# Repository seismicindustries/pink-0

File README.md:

<!--- View this project on [CADLAB.io](https://cadlab.io/project/1079). -->

# (s)pink-0

This repository contains the source code and the schematics for an Ableton Link to clock/reset converter.

And the necessary changes & hardware files for the spink-0 adaption

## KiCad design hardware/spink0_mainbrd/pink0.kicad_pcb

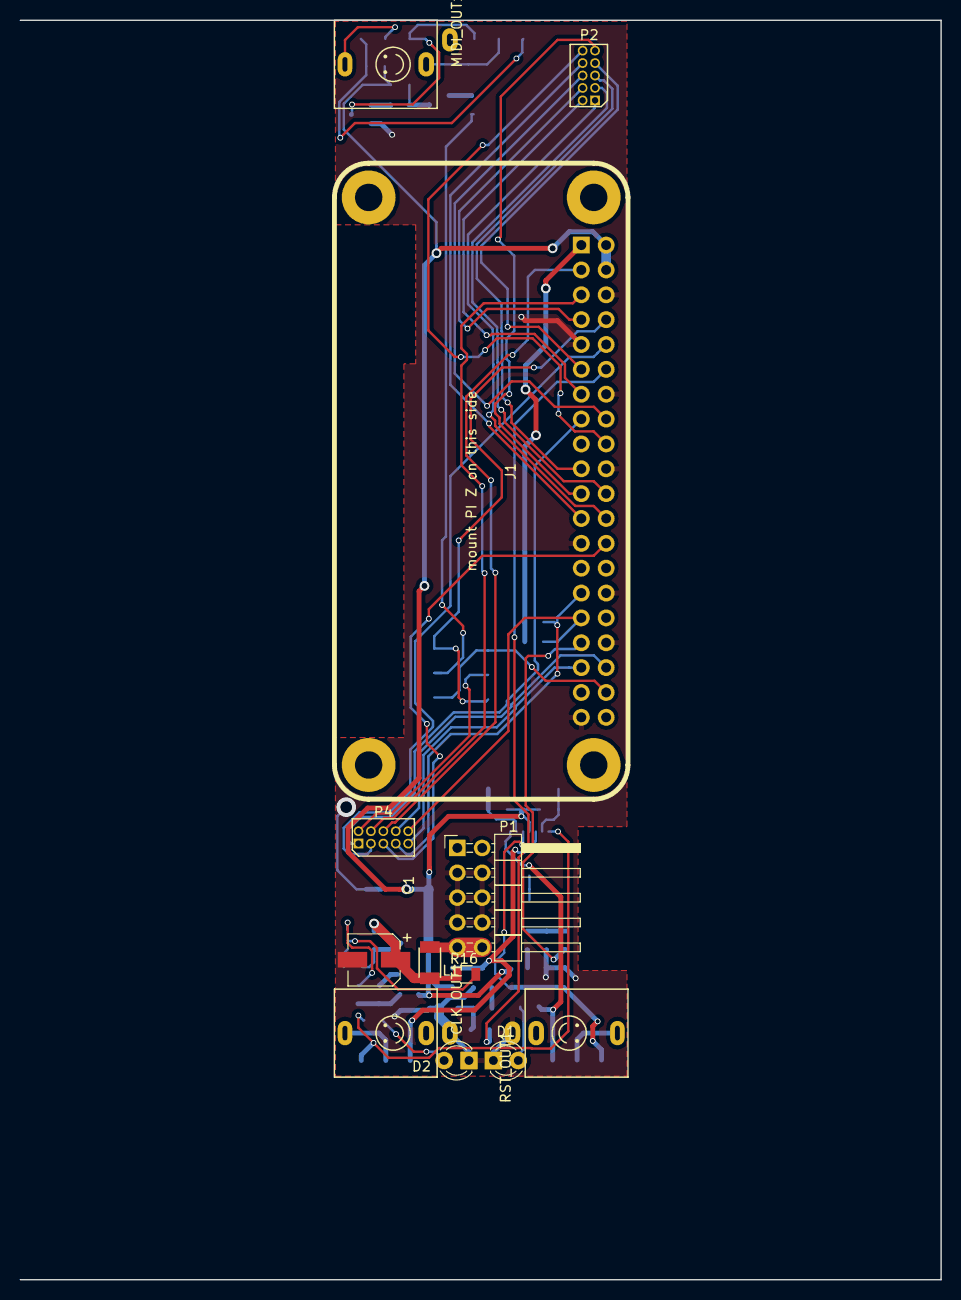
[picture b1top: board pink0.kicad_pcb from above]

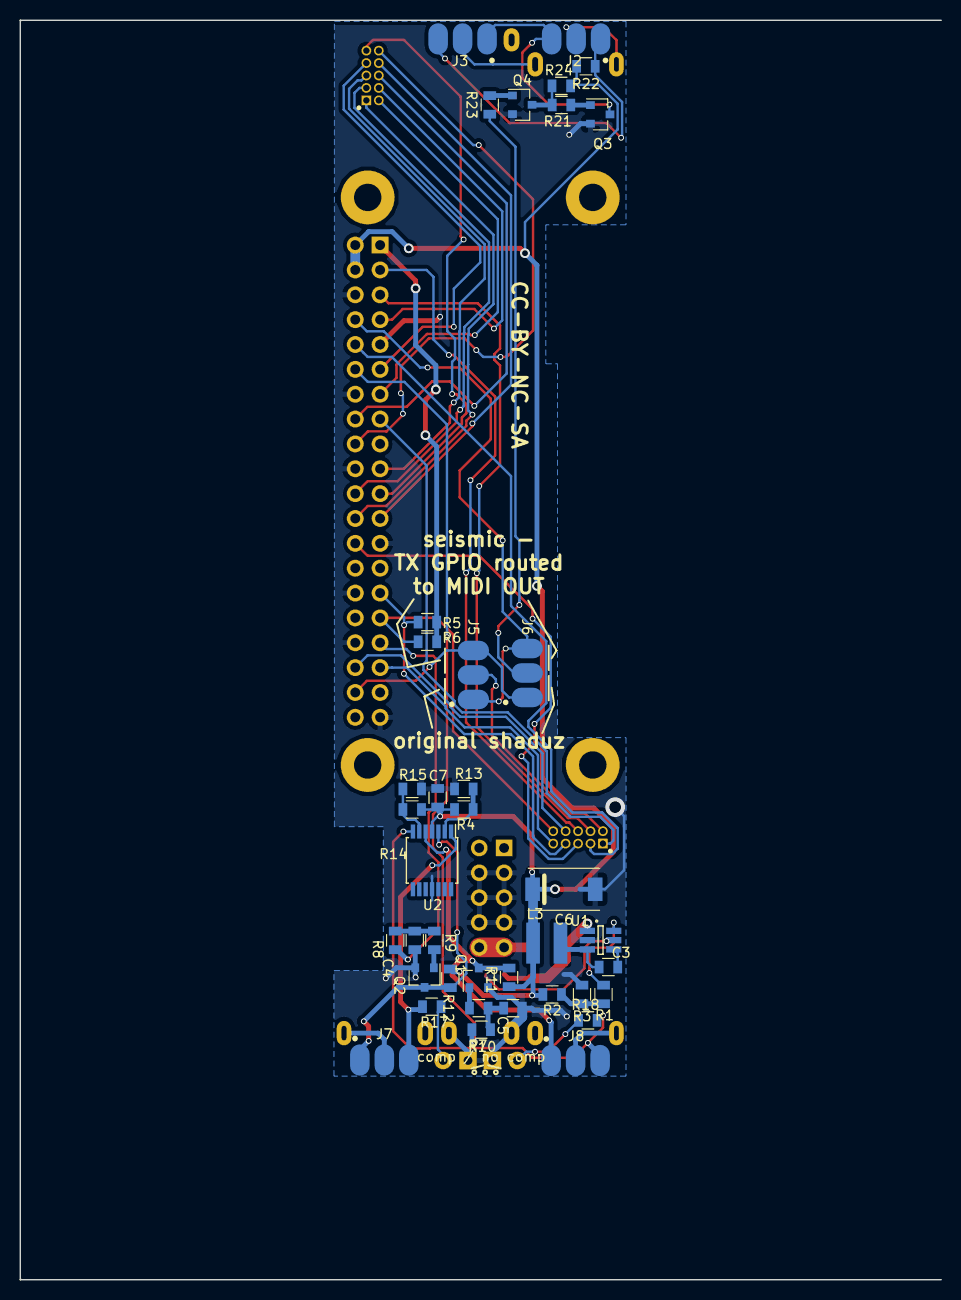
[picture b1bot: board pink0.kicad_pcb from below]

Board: 2 copper layers, 94.1 x 128.7 mm, 51 parts (39 on the bottom side), 56 nets.

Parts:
C1: 22u; CP_Elec_5x5.3
C3: 1u; C_0805
C4, C5: 33n; C_0805
C6: 22u; CP_Elec_7.3x4.3
C7: 100n; C_0805
CLK_OUT1: JACK_QINGPU; jack_qingpu
D1, D2: LED; LED_D3.0mm
J1: PI_ZERO
J2, J3, J5, J6, J7, J8: GS3; solderbridge
L1: INDUCTOR; Inductor_PSU_NLCV32T
L3: 6.8uH; Inductor_SRN4018TA_bourns
MIDI_OUT1: JACK_QINGPU; jack_qingpu
P1: CONN_02X05; Pin_Header_Angled_2x05_Pitch2.54mm_with_space_for_con
P2, P4: CONN_02X05; PINHEAD_10_pin_jtag_connector
Q1, Q2, Q3, Q4: BC849; SOT-23
R1: 75k; R_0805
R2: 40k2; R_0805
R3: 7k68; R_0805
R4, R7, R8, R9, R10, R11, R12, R13, R14, R15, R17, R18: 1k; R_0805
R5, R6, R21, R23, R24: 10k; R_0805
R16: 100k; R_0805
R22: 220; R_0805
RST_OUT1: JACK_QINGPU; jack_qingpu
U1: MP1469; SOT-23-6
U2: MCP6004; TSSOP-14_4.4x5mm_Pitch0.65mm

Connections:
+3V3: J1.1, R5.1, R6.1
+5V: C6.1, C7.2, J1.2, J1.4, L3.1, R2.2, R4.1, R11.2, R12.2, R14.1, R22.1, R24.2, U2.4
+12VA: C1.1, L1.1, R16.1, U1.1
CLK_OUT: J8.1, Q1.3, R11.1, U2.5
Earth: C1.2, C4.2, C5.2, C6.2, C7.1, CLK_OUT1.1, D1.1, D2.1, J1.6, J1.9, J1.14, J1.20, J1.25, J1.30, J1.34, J1.39, P1.3, P1.4, P1.5, P1.6, P1.7, P1.8, Q1.2, Q2.2, Q3.2, Q4.2, R3.1, R13.2, R15.2, RST_OUT1.1, U1.2, U2.11
GPIO2: J1.3, P4.6
GPIO3: J1.5, P4.4
GPIO4: J1.7, P2.4
GPIO5: J1.29, P4.7, R5.2
GPIO6: J1.31, P4.10, R6.2
GPIO7: J1.26, P4.5
GPIO8: J1.24, P2.1
GPIO9: J1.21, P2.9
GPIO10: J1.19, P2.5
GPIO11: J1.23, P2.8
GPIO14: J1.8, J5.1, J6.3
GPIO15: J1.10, P4.3
GPIO16: J1.36, P4.8
GPIO17: J1.11, P2.7
GPIO19: J1.35, P4.9
GPIO20: J1.38, J5.3, J6.1
GPIO22: J1.15, P4.1
GPIO23: J1.16, P2.6
GPIO24: J1.18, P2.10
GPIO25: J1.22, P2.3
GPIO27: J1.13, P2.2
unnamed: C3.1, L3.2, U1.3
unnamed: C3.2, U1.4
unnamed: C4.1, R8.1, R9.2
unnamed: C5.1, R7.1, R10.2
unnamed: CLK_OUT1.3, J8.2
unnamed: D1.2, R17.1
unnamed: D2.2, R18.1
unnamed: J2.1, J3.3, R22.2
unnamed: J2.2, MIDI_OUT1.3
unnamed: J2.3, J3.1, Q3.3
unnamed: J3.2, MIDI_OUT1.2
unnamed: J6.2, R23.2
unnamed: J7.2, RST_OUT1.3
unnamed: J7.3, R17.2, U2.1
unnamed: J8.3, R18.2, U2.7
unnamed: L1.2, P1.9, P1.10
unnamed: Q1.1, R10.1
unnamed: Q2.1, R9.1
unnamed: Q3.1, R21.1
unnamed: Q4.1, R23.1
unnamed: Q4.3, R21.2, R24.1
unnamed: R1.1, U1.6
unnamed: R1.2, R2.1, R3.2
unnamed: R4.2, R13.1, U2.2
unnamed: R14.2, R15.1, U2.6
unnamed: R16.2, U1.5
PWMA_L: J1.12, R7.2
PWMA_R: J1.33, R8.2
RST_OUT: J7.1, Q2.3, R12.1, U2.3
T_LED: J5.2, P4.2

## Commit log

2018-07-04 commit all changes from SI - (add spink hw files, addnet.php, modified UserInterfacePiZero.cpp, modeswitch stuff)
2018-07-04 changed readme
2018-07-04 changes/additions to installscript
2018-07-04 moved install.sh to correct location
2018-07-04 modeswitch DIR cleaned, BOM pdf added, comment out cadlab
2018-12-01 cleanup installer

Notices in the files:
hardware/spink0_mainbrd/pink0.kicad_pcb:
CC-BY-NC-SA
